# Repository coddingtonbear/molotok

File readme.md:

# Molotok: ATtiny85-based WS2812b Controller

I wake up both way before my partner and way before sunrise most mornings and need to see in my wardrobe to pick out clothes for the day.
To do this, I have to carefully aim my phone's flashlight into the closet, and, given that the process of putting on clothes generally requires that I have free hands, I've dropped my phone many times making a great deal of partner-waking noise.
So, I thought, why don't I fix this? I know I have at least a meter of neopixels available; can't basically any problem be fixed with a microcontroller and a bunch of leds?  This is that.

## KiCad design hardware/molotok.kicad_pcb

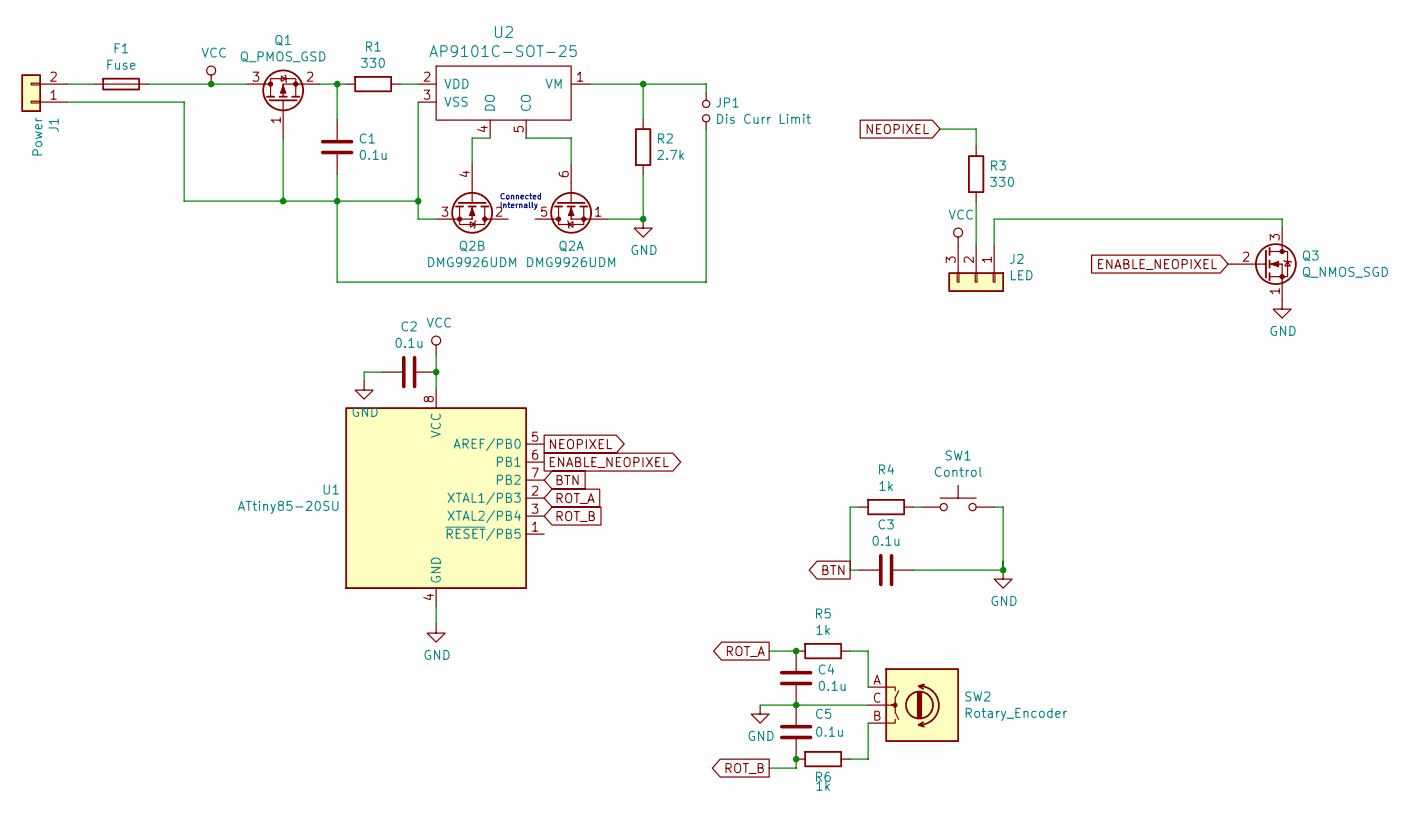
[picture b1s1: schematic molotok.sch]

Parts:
C1, C2, C3, C4, C5: 0.1u; 0805_Milling
F1: Fuse; R_1206_3216Metric_Pad1.42x1.75mm_HandSolder
J1: Power; JST_XH_B02B-XH-A_02x2.50mm_Straight_LargePads
J2: LED; JST_XH_B03B-XH-A_03x2.50mm_Straight_LargePads
JP1: Dis Curr Limit; SolderJumper-2_P1.3mm_Open_RoundedPad1.0x1.5mm
Q1: Q_PMOS_GSD; SuperSOT-3
Q2: DMG9926UDM; SOT-23-6_Handsoldering
Q3: Q_NMOS_SGD; PSMN5R4-25YLD
R1, R3: 330; 0805_Milling
R2: 2.7k; 0805_Milling
R4, R5, R6: 1k; 0805_Milling
SW1: Control; SMD_RED_TACTILE_SWITCH
SW2: Rotary_Encoder; PES12
U1: ATtiny85-20SU; SOIJ-8_5.3x5.3mm_P1.27mm
U2: AP9101C-SOT-25; SOT-23-5_HandSoldering

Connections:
BTN: C3.1, R4.2, U1.7 (PB2)
ENABLE_NEOPIXEL: Q3.2 (G), U1.6 (PB1)
GND: C2.1, C3.2, C4.2, C5.1, Q2.1 (S), Q3.1 (S), R2.2, SW1.2, SW2.C, U1.4 (GND)
NEOPIXEL: R3.1, U1.5 (AREF/PB0)
unnamed: C1.1, Q1.2 (S), R1.2
unnamed: C1.2, J1.1, JP1.2, Q1.1 (G), Q2.3 (S), U2.3 (VSS)
unnamed: F1.2, J1.2
unnamed: J2.1, Q3.3 (D)
unnamed: J2.2, R3.2
unnamed: JP1.1, R2.1, U2.1 (VM)
unnamed: Q2.4 (G), U2.4 (DO)
unnamed: Q2.6 (G), U2.5 (CO)
unnamed: R1.1, U2.2 (VDD)
unnamed: R4.1, SW1.1
unnamed: R5.1, SW2.A
unnamed: R6.1, SW2.B
ROT_A: C4.1, R5.2, U1.2 (XTAL1/PB3)
ROT_B: C5.2, R6.2, U1.3 (XTAL2/PB4)
VCC: C2.2, F1.1, J2.3, Q1.3 (D), U1.8 (VCC)

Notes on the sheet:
Connected Internally

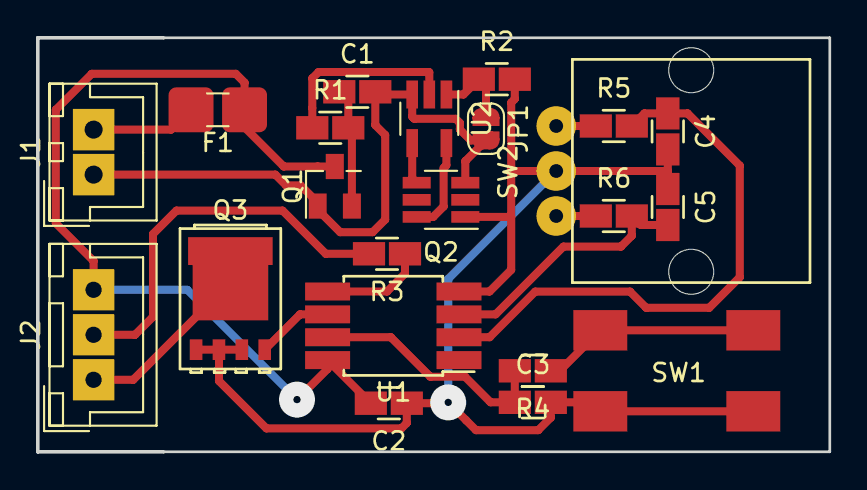
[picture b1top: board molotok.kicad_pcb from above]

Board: 2 copper layers, 44.0 x 23.0 mm, 22 parts (0 on the bottom side), 19 nets.

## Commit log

2019-01-27 And so it begins...
2019-01-27 Words.
2019-01-27 Punctuation.
2019-01-27 Reversing mosfet orientation to be correct.
2019-01-27 Use a rotary encoder instead of a potentiometer for control.
2019-01-28 Adding firmware.
2019-01-31 Adding fuse.
